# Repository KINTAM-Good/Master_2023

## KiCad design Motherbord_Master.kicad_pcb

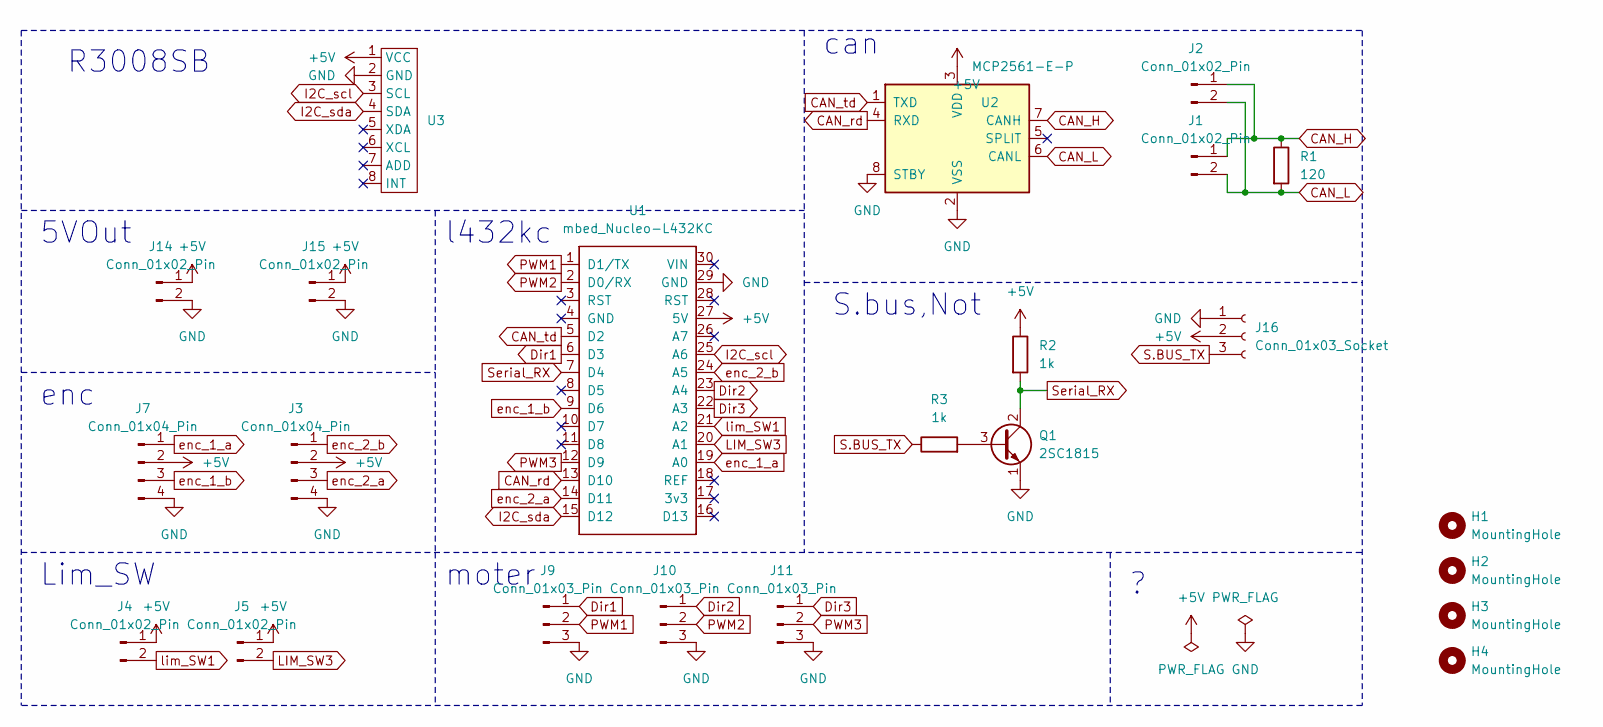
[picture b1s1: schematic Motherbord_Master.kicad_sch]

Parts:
H1, H2, H3, H4: MountingHole; MountingHole_3.2mm_M3_Pad_Via
J1, J2, J4, J5, J14, J15: Conn_01x02_Pin; JST_XH_S2B-XH-A_1x02_P2.50mm_Horizontal
J3, J7: Conn_01x04_Pin; JST_XH_S4B-XH-A_1x04_P2.50mm_Horizontal
J9, J10, J11: Conn_01x03_Pin; JST_XH_S3B-XH-A_1x03_P2.50mm_Horizontal
J16: Conn_01x03_Socket; R3008SB
Q1: 2SC1815; TO-92_Inline
R1: 120; R_Axial_DIN0207_L6.3mm_D2.5mm_P7.62mm_Horizontal
R2, R3: 1k; R_Axial_DIN0207_L6.3mm_D2.5mm_P7.62mm_Horizontal
U1: mbed_Nucleo-L432KC; MODULE_NUCLEO-L432KC
U2: MCP2561-E-P; DIP-8_W7.62mm
U3: MPU6050

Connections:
+5V: J3.2, J4.1, J5.1, J7.2, J14.1, J15.1, J16.2, R2.1, U1.27 (5V), U2.3 (VDD), U3.1 (VCC)
CAN_H: J1.1, J2.1, R1.1, U2.7 (CANH)
CAN_L: J1.2, J2.2, R1.2, U2.6 (CANL)
CAN_rd: U1.13 (D10), U2.4 (RXD)
CAN_td: U1.5 (D2), U2.1 (TXD)
Dir1: J9.1, U1.6 (D3)
Dir2: J10.1, U1.23 (A4)
Dir3: J11.1, U1.22 (A3)
GND: J3.4, J7.4, J9.3, J10.3, J11.3, J14.2, J15.2, J16.1, Q1.1 (E), U1.29 (GND), U2.2 (VSS), U2.8 (STBY), U3.2 (GND)
I2C_scl: U1.25 (A6), U3.3 (SCL)
I2C_sda: U1.15 (D12), U3.4 (SDA)
LIM_SW3: J5.2, U1.20 (A1)
unnamed: Q1.3 (B), R3.2
PWM1: J9.2, U1.1 (D1/TX)
PWM2: J10.2, U1.2 (D0/RX)
PWM3: J11.2, U1.12 (D9)
S.BUS_TX: J16.3, R3.1
Serial_RX: Q1.2 (C), R2.2, U1.7 (D4)
enc_1_a: J7.1, U1.19 (A0)
enc_1_b: J7.3, U1.9 (D6)
enc_2_a: J3.3, U1.14 (D11)
enc_2_b: J3.1, U1.24 (A5)
lim_SW1: J4.2, U1.21 (A2)

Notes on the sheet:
Lim_SW
R3008SB
moter
5VOut
S.bus,Not
enc
can
l432kc

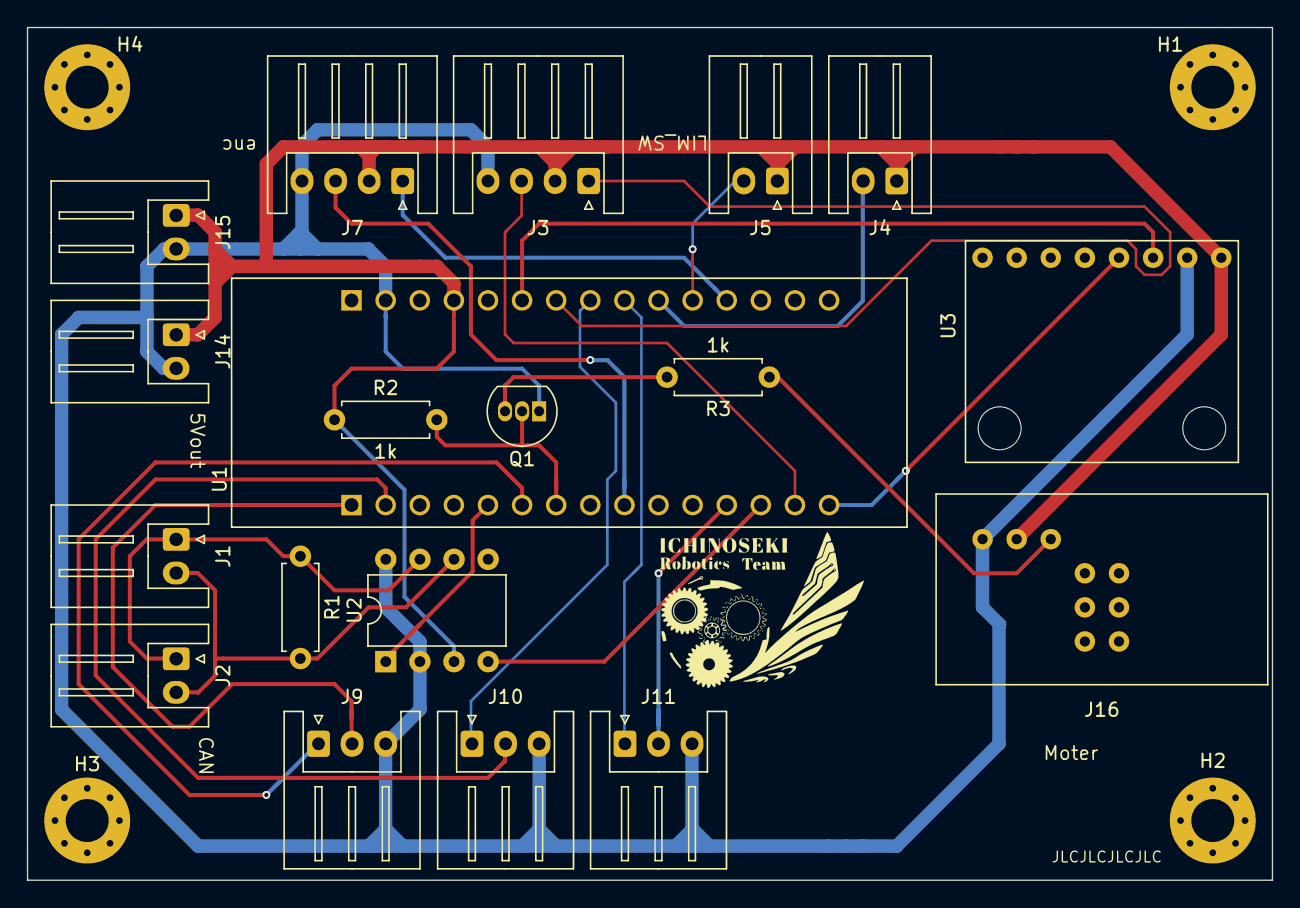
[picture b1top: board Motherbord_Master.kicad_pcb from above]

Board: 2 copper layers, 92.7 x 63.5 mm, 24 parts (0 on the bottom side), 23 nets.

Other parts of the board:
J8: Logo; INCT
